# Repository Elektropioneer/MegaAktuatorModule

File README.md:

# MegaAktuatorModule
Module for the Arduino MEGA to support EP modules

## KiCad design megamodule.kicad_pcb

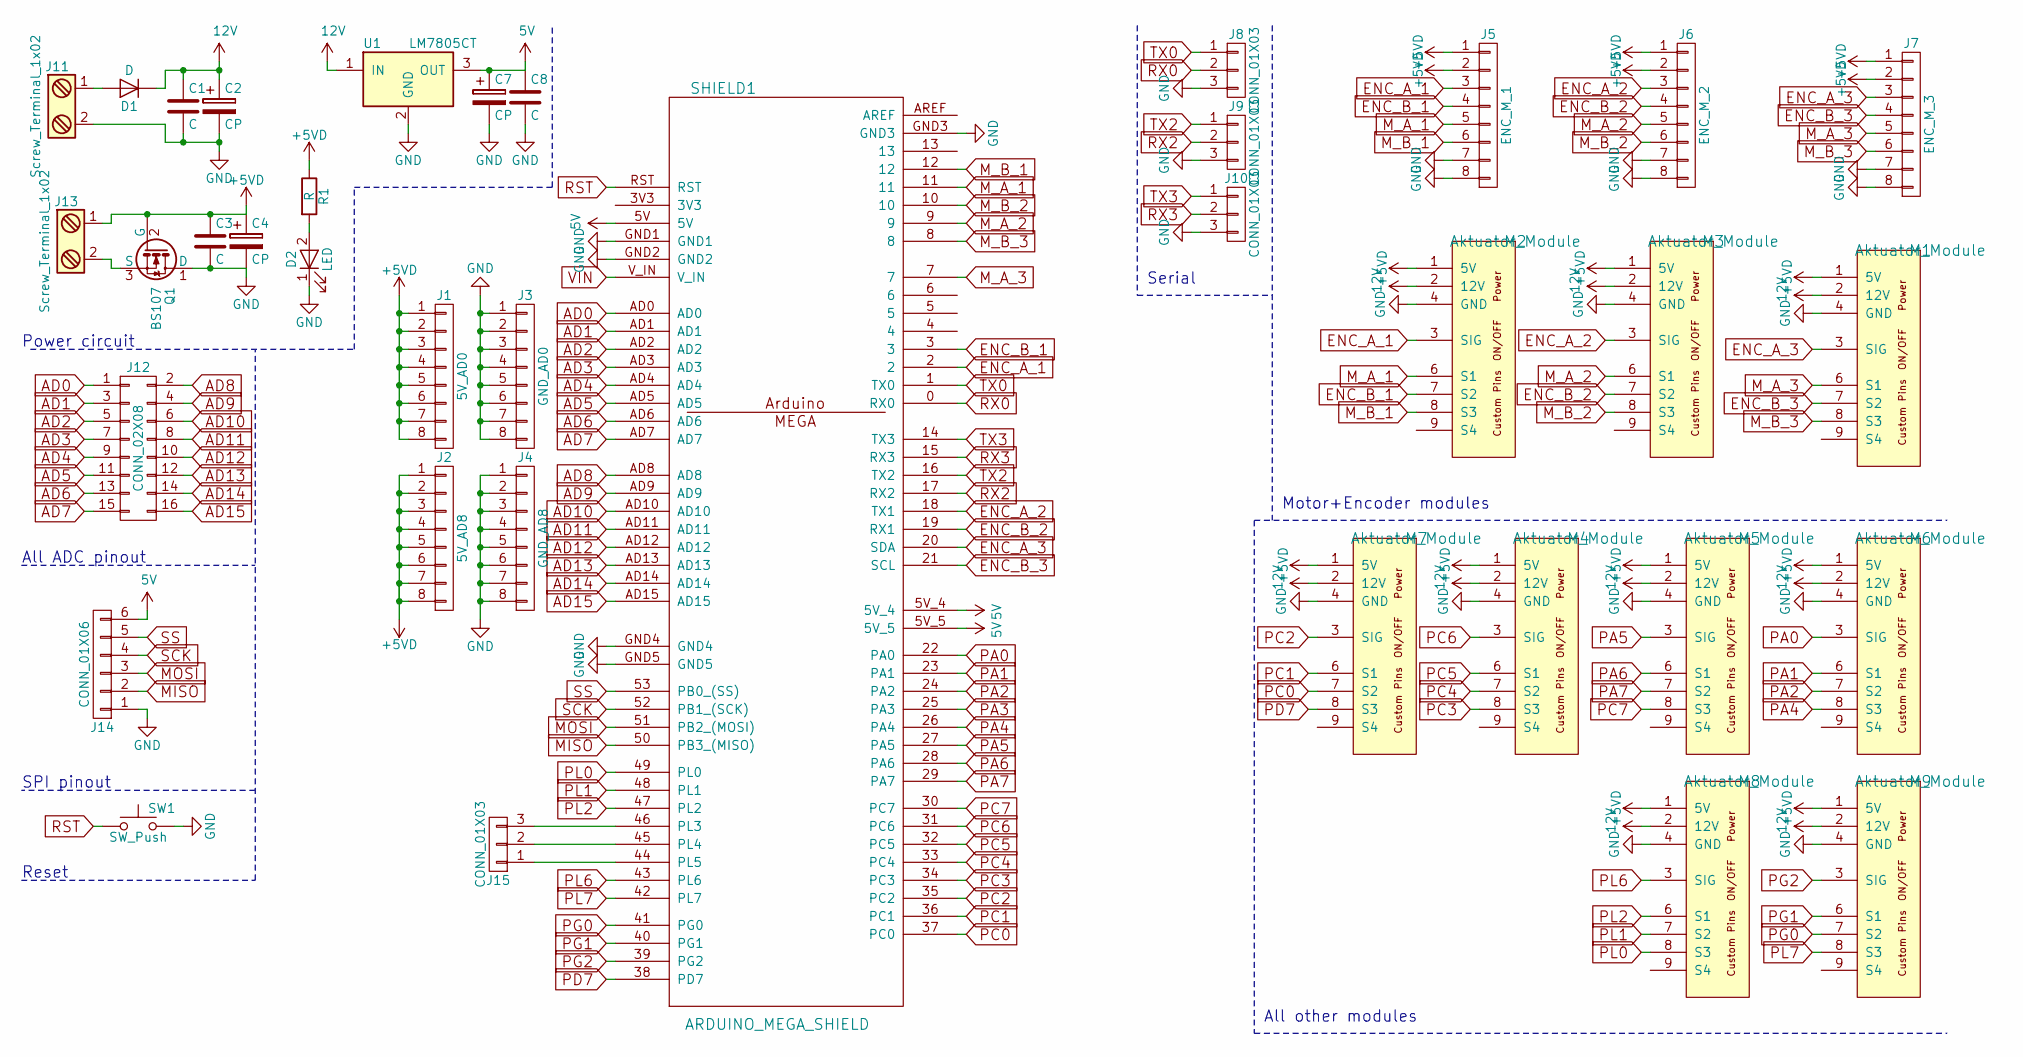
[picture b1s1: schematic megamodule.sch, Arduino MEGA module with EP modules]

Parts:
C1, C3, C8: C; C_0805
C2, C4, C7: CP; CP_Elec_6.3x4.5
D1: D; D_SMB_Standard
D2: LED; LED_0805
J1: 5V_AD0; Pin_Header_Straight_1x08_Pitch2.54mm
J2: 5V_AD8; Pin_Header_Straight_1x08_Pitch2.54mm
J3: GND_AD0; Pin_Header_Straight_1x08_Pitch2.54mm
J4: GND_AD8; Pin_Header_Straight_1x08_Pitch2.54mm
J5: ENC_M_1; Pin_Header_Straight_1x08_Pitch2.54mm
J6: ENC_M_2; Pin_Header_Straight_1x08_Pitch2.54mm
J7: ENC_M_3; Pin_Header_Straight_1x08_Pitch2.54mm
J8, J9, J10: CONN_01X03; Pin_Header_Straight_1x03_Pitch2.54mm
J11, J13: Screw_Terminal_1x02; TerminalBlock_Pheonix_MKDS1.5-2pol
J12: CONN_02X08; Pin_Header_Straight_2x08_Pitch1.27mm_SMD
J14: CONN_01X06; Pin_Header_Straight_1x06_Pitch2.00mm_SMD_Pin1Right
J15: CONN_01X03; GS3
M1, M2, M3, M4, M5, M6, M7, M8, M9: Aktuator_Module
Q1: BS107; TO-252-2Lead
R1: R; R_0805
SHIELD1: ARDUINO_MEGA_SHIELD; ARDUINO MEGA SHIELD
SW1: SW_Push; SW_DIP_x1_W7.62mm_Slide_LowProfile
U1: LM7805CT; TO-252-2Lead

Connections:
5V: C7.1, C8.1, J14.6, SHIELD1.5V, SHIELD1.5V_4, SHIELD1.5V_5, U1.3 (OUT)
12V: C1.1, C2.1, D1.1 (K), M1.2 (12V), M2.2 (12V), M3.2 (12V), M4.2 (12V), M5.2 (12V), M6.2 (12V), M7.2 (12V), M8.2 (12V), M9.2 (12V), U1.1 (IN)
+5VD: C3.1, C4.1, J1.1, J1.2, J1.3, J1.4, J1.5, J1.6, J1.7, J1.8, J2.1, J2.2, J2.3, J2.4, J2.5, J2.6, J2.7, J2.8, J5.1, J5.2, J6.1, J6.2, J7.1, J7.2, J13.1, M1.1 (5V), M2.1 (5V), M3.1 (5V), M4.1 (5V), M5.1 (5V), M6.1 (5V), M7.1 (5V), M8.1 (5V), M9.1 (5V), Q1.2 (G), R1.1
AD0: J12.1, SHIELD1.AD0
AD1: J12.3, SHIELD1.AD1
AD2: J12.5, SHIELD1.AD2
AD3: J12.7, SHIELD1.AD3
AD4: J12.9, SHIELD1.AD4
AD5: J12.11, SHIELD1.AD5
AD6: J12.13, SHIELD1.AD6
AD7: J12.15, SHIELD1.AD7
AD8: J12.2, SHIELD1.AD8
AD9: J12.4, SHIELD1.AD9
AD10: J12.6, SHIELD1.AD10
AD11: J12.8, SHIELD1.AD11
AD12: J12.10, SHIELD1.AD12
AD13: J12.12, SHIELD1.AD13
AD14: J12.14, SHIELD1.AD14
AD15: J12.16, SHIELD1.AD15
ENC_A_1: J5.3, M2.3 (SIG), SHIELD1.2
ENC_A_2: J6.3, M3.3 (SIG), SHIELD1.18 (TX1)
ENC_A_3: J7.3, M1.3 (SIG), SHIELD1.20 (SDA)
ENC_B_1: J5.4, M2.7 (S2), SHIELD1.3
ENC_B_2: J6.4, M3.7 (S2), SHIELD1.19 (RX1)
ENC_B_3: J7.4, M1.7 (S2), SHIELD1.21 (SCL)
GND: C1.2, C2.2, C3.2, C4.2, C7.2, C8.2, D2.1 (K), J3.1, J3.2, J3.3, J3.4, J3.5, J3.6, J3.7, J3.8, J4.1, J4.2, J4.3, J4.4, J4.5, J4.6, J4.7, J4.8, J5.7, J5.8, J6.7, J6.8, J7.7, J7.8, J8.3, J9.3, J10.3, J11.2, J14.1, M1.4 (GND), M2.4 (GND), M3.4 (GND), M4.4 (GND), M5.4 (GND), M6.4 (GND), M7.4 (GND), M8.4 (GND), M9.4 (GND), Q1.1 (D), SHIELD1.GND1, SHIELD1.GND2, SHIELD1.GND3, SHIELD1.GND4, SHIELD1.GND5, SW1.2, U1.2 (GND)
MISO: J14.2, SHIELD1.50 (PB3_(MISO))
MOSI: J14.3, SHIELD1.51 (PB2_(MOSI))
M_A_1: J5.5, M2.6 (S1), SHIELD1.11
M_A_2: J6.5, M3.6 (S1), SHIELD1.9
M_A_3: J7.5, M1.6 (S1), SHIELD1.7
M_B_1: J5.6, M2.8 (S3), SHIELD1.12
M_B_2: J6.6, M3.8 (S3), SHIELD1.10
M_B_3: J7.6, M1.8 (S3), SHIELD1.8
unnamed: D1.2 (A), J11.1
unnamed: D2.2 (A), R1.2
unnamed: J13.2, Q1.3 (S)
unnamed: J15.1, SHIELD1.44 (PL5)
unnamed: J15.2, SHIELD1.45 (PL4)
unnamed: J15.3, SHIELD1.46 (PL3)
PA0: M6.3 (SIG), SHIELD1.22 (PA0)
PA1: M6.6 (S1), SHIELD1.23 (PA1)
PA2: M6.7 (S2), SHIELD1.24 (PA2)
PA4: M6.8 (S3), SHIELD1.26 (PA4)
PA5: M5.3 (SIG), SHIELD1.27 (PA5)
PA6: M5.6 (S1), SHIELD1.28 (PA6)
PA7: M5.7 (S2), SHIELD1.29 (PA7)
PC0: M7.7 (S2), SHIELD1.37 (PC0)
PC1: M7.6 (S1), SHIELD1.36 (PC1)
PC2: M7.3 (SIG), SHIELD1.35 (PC2)
PC3: M4.8 (S3), SHIELD1.34 (PC3)
PC4: M4.7 (S2), SHIELD1.33 (PC4)
PC5: M4.6 (S1), SHIELD1.32 (PC5)
PC6: M4.3 (SIG), SHIELD1.31 (PC6)
PC7: M5.8 (S3), SHIELD1.30 (PC7)
PD7: M7.8 (S3), SHIELD1.38 (PD7)
PG0: M9.7 (S2), SHIELD1.41 (PG0)
PG1: M9.6 (S1), SHIELD1.40 (PG1)
PG2: M9.3 (SIG), SHIELD1.39 (PG2)
PL0: M8.8 (S3), SHIELD1.49 (PL0)
PL1: M8.7 (S2), SHIELD1.48 (PL1)
PL2: M8.6 (S1), SHIELD1.47 (PL2)
PL6: M8.3 (SIG), SHIELD1.43 (PL6)
PL7: M9.8 (S3), SHIELD1.42 (PL7)
RST: SHIELD1.RST, SW1.1
RX0: J8.2, SHIELD1.0 (RX0)
RX2: J9.2, SHIELD1.17 (RX2)
RX3: J10.2, SHIELD1.15 (RX3)
SCK: J14.4, SHIELD1.52 (PB1_(SCK))
SS: J14.5, SHIELD1.53 (PB0_(SS))
TX0: J8.1, SHIELD1.1 (TX0)
TX2: J9.1, SHIELD1.16 (TX2)
TX3: J10.1, SHIELD1.14 (TX3)

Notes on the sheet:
Reset
SPI pinout
All ADC pinout
Power circuit
Serial
Motor+Encoder modules
All other modules

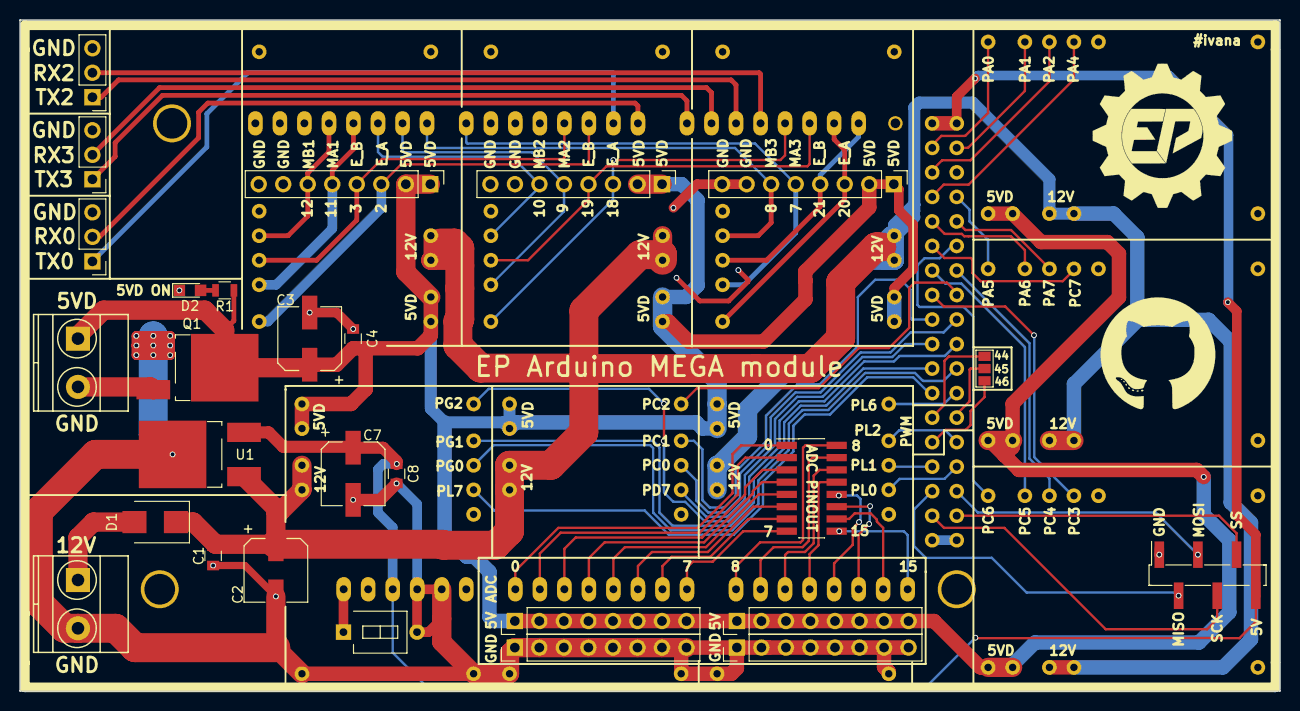
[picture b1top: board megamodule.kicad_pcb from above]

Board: 2 copper layers, 130.5 x 69.5 mm, 37 parts (0 on the bottom side), 73 nets.

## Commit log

2018-03-11 Added everything
